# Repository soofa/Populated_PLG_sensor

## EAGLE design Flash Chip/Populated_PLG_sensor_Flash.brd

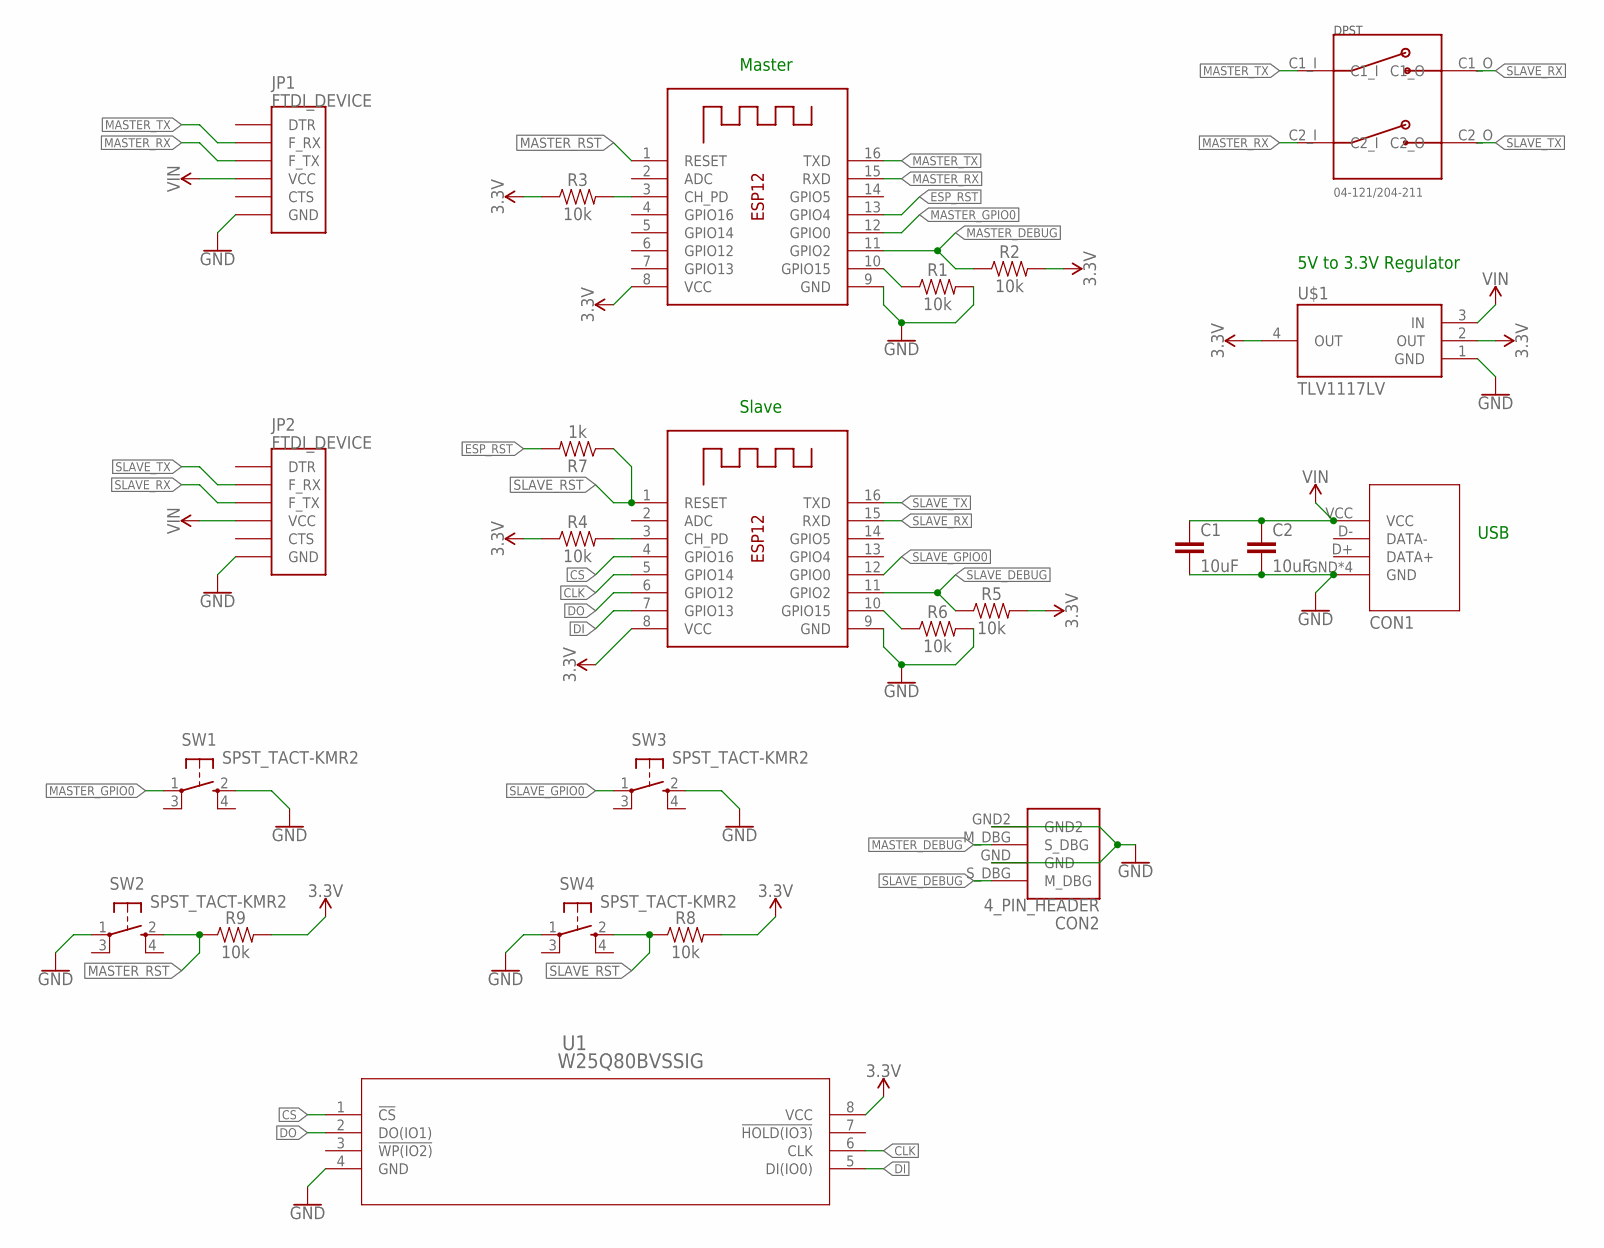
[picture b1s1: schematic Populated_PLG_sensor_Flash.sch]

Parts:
C1, C2: 10uF; 0603
CON1: USB_MOLEX_0480372200
CON2: 4_PIN_HEADER; 22-23-2041
DPST1: DPST_1POS
JP1, JP2: FTDI_DEVICE; FTDI_DEVICE_SIDE
R1, R2, R3, R4, R5, R6, R8, R9: 10k; 0603
R7: 1k; 0603
SW1, SW2, SW3, SW4: SPST_TACT-KMR2; KMR2
U1: W25Q80BVSSIG; WIN_SS-8
U$1: TLV1117LV; SOT223
X1, X2: ESP-12

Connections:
3.3V: R2.2, R3.1, R4.1, R5.2, R8.2, R9.2, U1.8 (VCC), U$1.2 (OUT), U$1.4 (OUT), X1.8 (VCC), X2.8 (VCC)
CLK: U1.6 (CLK), X2.5 (GPIO14)
CS: U1.1 (!CS), X2.4 (GPIO16)
DI: U1.5 (DI(IO0)), X2.7 (GPIO13)
DO: U1.2 (DO(IO1)), X2.6 (GPIO12)
ESP_RST: R7.2, X1.13 (GPIO4)
GND: C1.2, C2.2, CON1.GND, CON1.GND2 (GND), CON1.GND3 (GND), CON1.GND4 (GND), CON2.GND, CON2.GND2, JP1.P$6 (GND), JP2.P$6 (GND), R1.2, R6.2, SW1.2 (S), SW2.1, SW3.2 (S), SW4.1, U1.4 (GND), U$1.1 (GND), X1.9 (GND), X2.9 (GND)
MASTER_DEBUG: CON2.M_DBG (S_DBG), R2.1, X1.11 (GPIO2)
MASTER_GPIO0: SW1.1, X1.12 (GPIO0)
MASTER_RST: R9.1, SW2.2 (S), X1.1 (RESET)
MASTER_RX: DPST1.C2_I, JP1.P$3 (F_TX), X1.15 (RXD)
MASTER_TX: DPST1.C1_I, JP1.P$2 (F_RX), X1.16 (TXD)
unnamed: R3.2, X1.3 (CH_PD)
unnamed: R1.1, X1.10 (GPIO15)
unnamed: R4.2, X2.3 (CH_PD)
unnamed: R6.1, X2.10 (GPIO15)
SLAVE_DEBUG: CON2.S_DBG (M_DBG), R5.1, X2.11 (GPIO2)
SLAVE_GPIO0: SW3.1, X2.12 (GPIO0)
SLAVE_RST: R7.1, R8.1, SW4.2 (S), X2.1 (RESET)
SLAVE_RX: DPST1.C1_O, JP2.P$3 (F_TX), X2.15 (RXD)
SLAVE_TX: DPST1.C2_O, JP2.P$2 (F_RX), X2.16 (TXD)
VIN: C1.1, C2.1, CON1.VCC, JP1.P$4 (VCC), JP2.P$4 (VCC), U$1.3 (IN)

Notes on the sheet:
Master
Slave
USB
5V to 3.3V Regulator

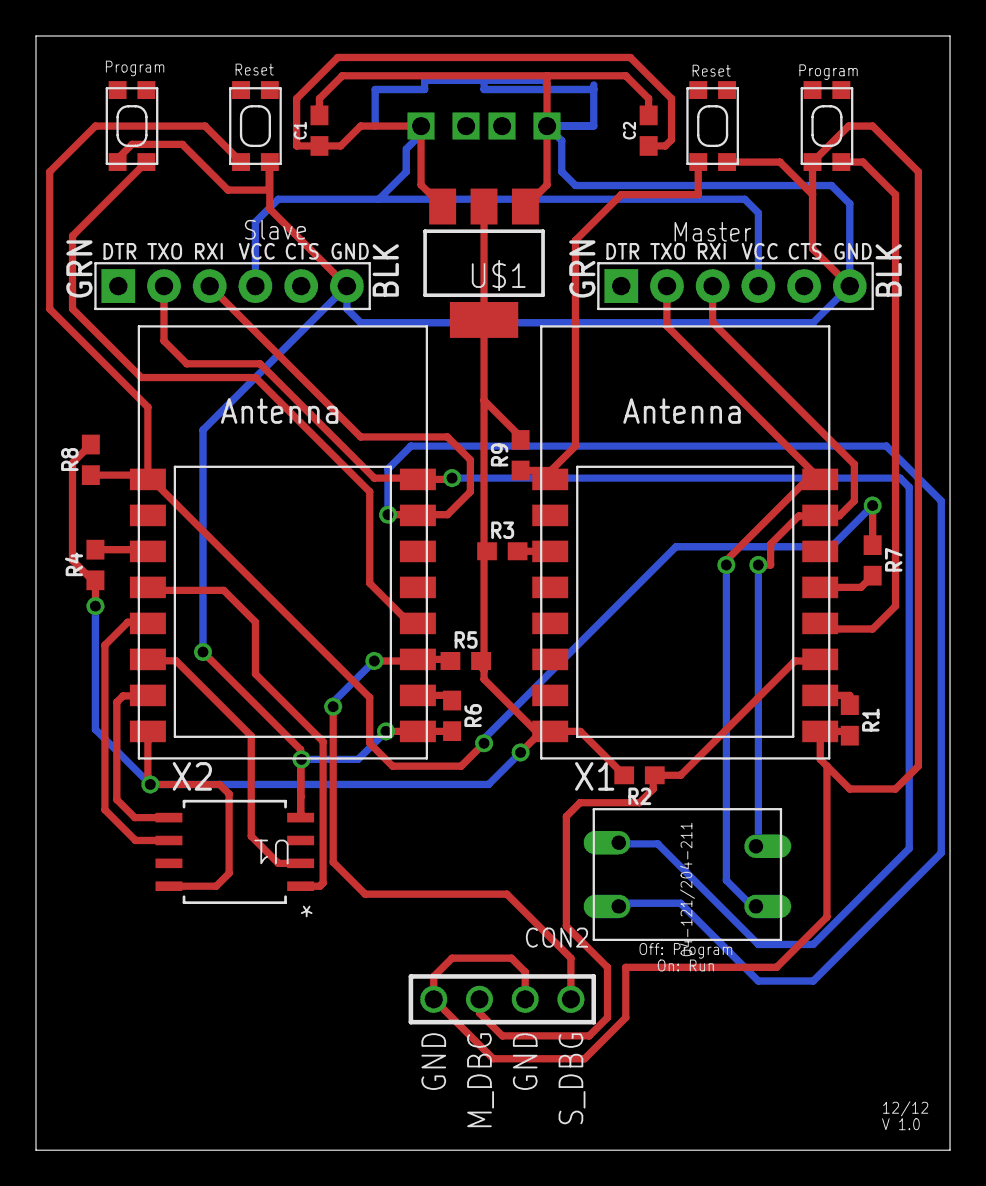
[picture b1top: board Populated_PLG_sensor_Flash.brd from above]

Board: 2 copper layers, 50.8 x 61.9 mm, 24 parts (1 on the bottom side), 22 nets.

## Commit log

2017-12-12 Updated layout
    Incomplete, uploading for Rob to look at
2017-12-12 Improved
2017-12-12 Added logo, button & switch labels
2017-12-12 Update with gerbers
2017-12-12 Fixed Clearance issue
2017-12-13 Added bom
2017-12-14 Added boards with SPI flash and SD
    There are sub-folders holding a board using SPI flash, and one with both SD and SPI flash.

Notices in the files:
parts and their libraries:
SparkFun-Resistors: Licensing: Creative Commons ShareAlike 4.0 International - https://creativecommons.org/licenses/by-sa/4.0
